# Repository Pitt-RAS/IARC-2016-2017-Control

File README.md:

IARC 2016-2017 Orbitty Shield Carrier Board

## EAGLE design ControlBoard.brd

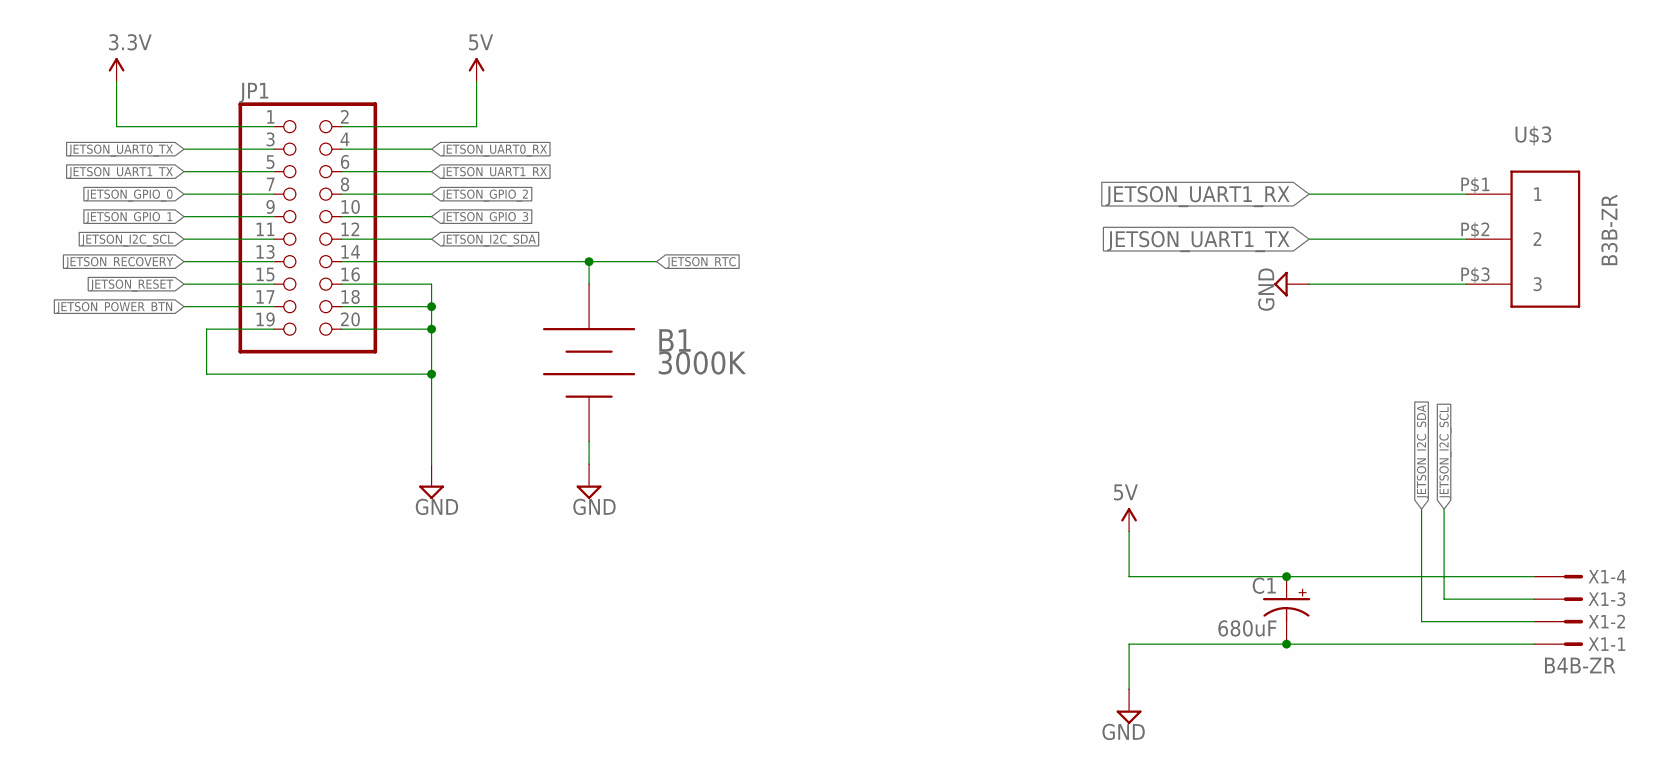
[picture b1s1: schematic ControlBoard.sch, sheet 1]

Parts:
B1: 3000K
C1: 680uF; CPOL-RADIAL-1000UF-25V
JP1: PINHD-2X10; 2X10
U$3: B3B-ZR; 3PIN-1.5MM
X1: B4B-ZR

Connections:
3.3V: JP1.1; also elsewhere on the board
5V: C1.+, JP1.2, X1.4; also elsewhere on the board
GND: B1.-, C1.-, JP1.16, JP1.18, JP1.19, JP1.20, U$3.P$3 (3), X1.1; also elsewhere on the board
JETSON_GPIO_0: JP1.7
JETSON_GPIO_1: JP1.9
JETSON_GPIO_2: JP1.8
JETSON_GPIO_3: JP1.10
JETSON_I2C_SCL: JP1.11, X1.3; also elsewhere on the board
JETSON_I2C_SDA: JP1.12, X1.2; also elsewhere on the board
JETSON_POWER_BTN: JP1.17
JETSON_RECOVERY: JP1.13
JETSON_RESET: JP1.15
JETSON_RTC: B1.+, JP1.14
JETSON_UART0_RX: JP1.4; also elsewhere on the board
JETSON_UART0_TX: JP1.3; also elsewhere on the board
JETSON_UART1_RX: JP1.6, U$3.P$1 (1)
JETSON_UART1_TX: JP1.5, U$3.P$2 (2)

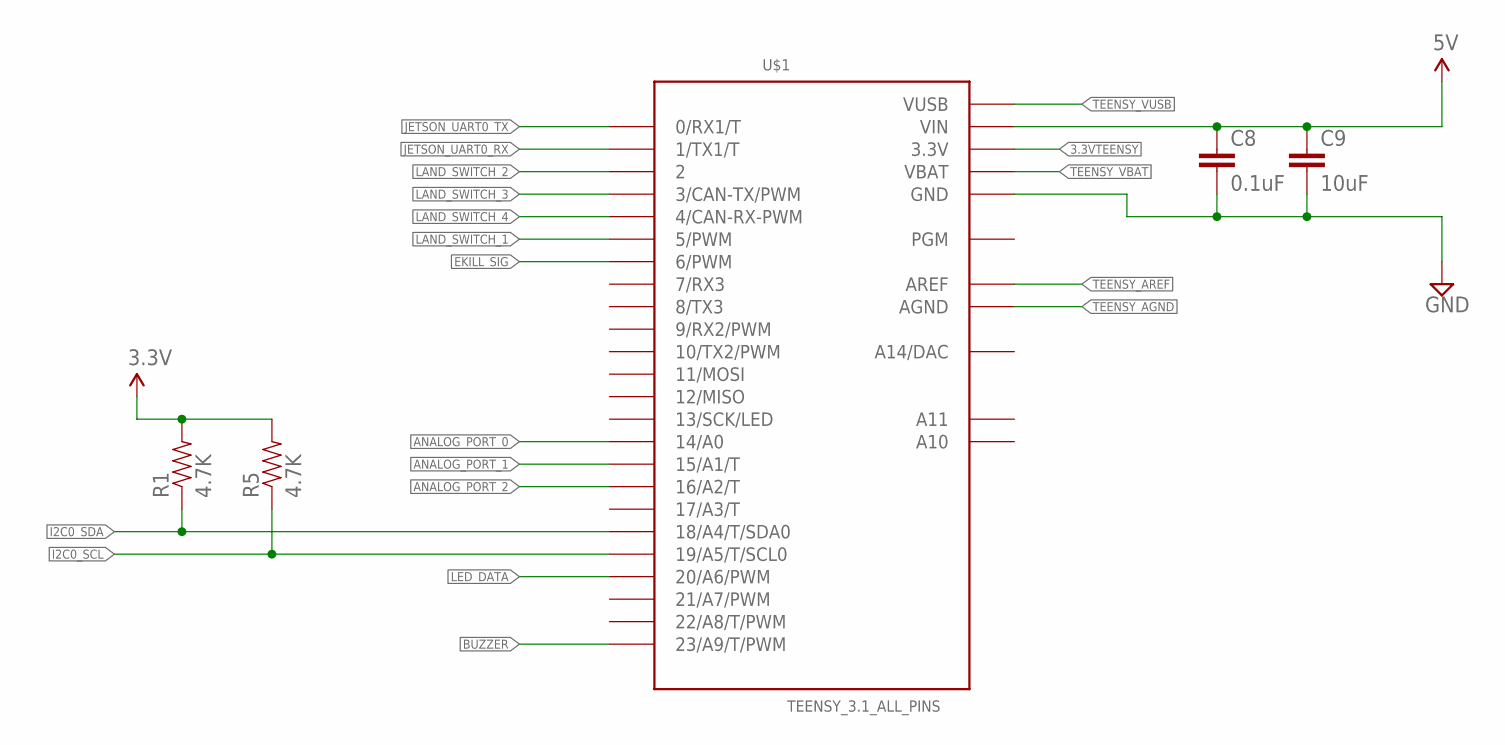
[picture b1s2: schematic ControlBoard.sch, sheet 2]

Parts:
C8: 0.1uF; 0603-CAP
C9: 10uF; 0603-CAP
R1, R5: 4.7K; 0603-RES
U$1: TEENSY_3.1_ALL_PINS; TEENSY3-ALL_PINS

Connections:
3.3V: R1.2, R5.2; also elsewhere on the board
3.3VTEENSY: U$1.3.3V, U$1.3.3V1 (3.3V)
5V: C8.1, C9.1, U$1.VIN; also elsewhere on the board
ANALOG_PORT_0: U$1.14/A0; also elsewhere on the board
ANALOG_PORT_1: U$1.15/A1 (15/A1/T); also elsewhere on the board
ANALOG_PORT_2: U$1.16/A2 (16/A2/T); also elsewhere on the board
BUZZER: U$1.23/A9 (23/A9/T/PWM); also elsewhere on the board
EKILL_SIG: U$1.6 (6/PWM); also elsewhere on the board
GND: C8.2, C9.2, U$1.GND, U$1.GND1 (GND); also elsewhere on the board
I2C0_SCL: R5.1, U$1.19/A5 (19/A5/T/SCL0); also elsewhere on the board
I2C0_SDA: R1.1, U$1.18/A4 (18/A4/T/SDA0); also elsewhere on the board
JETSON_UART0_RX: U$1.1 (1/TX1/T); also elsewhere on the board
JETSON_UART0_TX: U$1.0 (0/RX1/T); also elsewhere on the board
LAND_SWITCH_1: U$1.5 (5/PWM); also elsewhere on the board
LAND_SWITCH_2: U$1.2; also elsewhere on the board
LAND_SWITCH_3: U$1.3 (3/CAN-TX/PWM); also elsewhere on the board
LAND_SWITCH_4: U$1.4 (4/CAN-RX-PWM); also elsewhere on the board
LED_DATA: U$1.20/A6 (20/A6/PWM); also elsewhere on the board
TEENSY_AGND: U$1.AGND
TEENSY_AREF: U$1.AREF
TEENSY_VBAT: U$1.VBAT
TEENSY_VUSB: U$1.VUSB

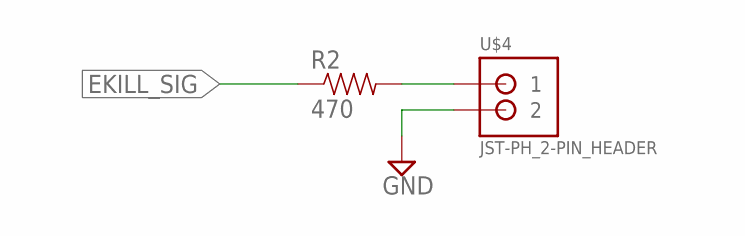
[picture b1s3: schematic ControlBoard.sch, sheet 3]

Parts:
R2: 470; 0603-RES
U$4: JST-PH_2-PIN_HEADER; JST_B2B-PH_HEADER

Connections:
EKILL_SIG: R2.1; also elsewhere on the board
GND: U$4.P2 (2); also elsewhere on the board
unnamed: R2.2, U$4.P1 (1)

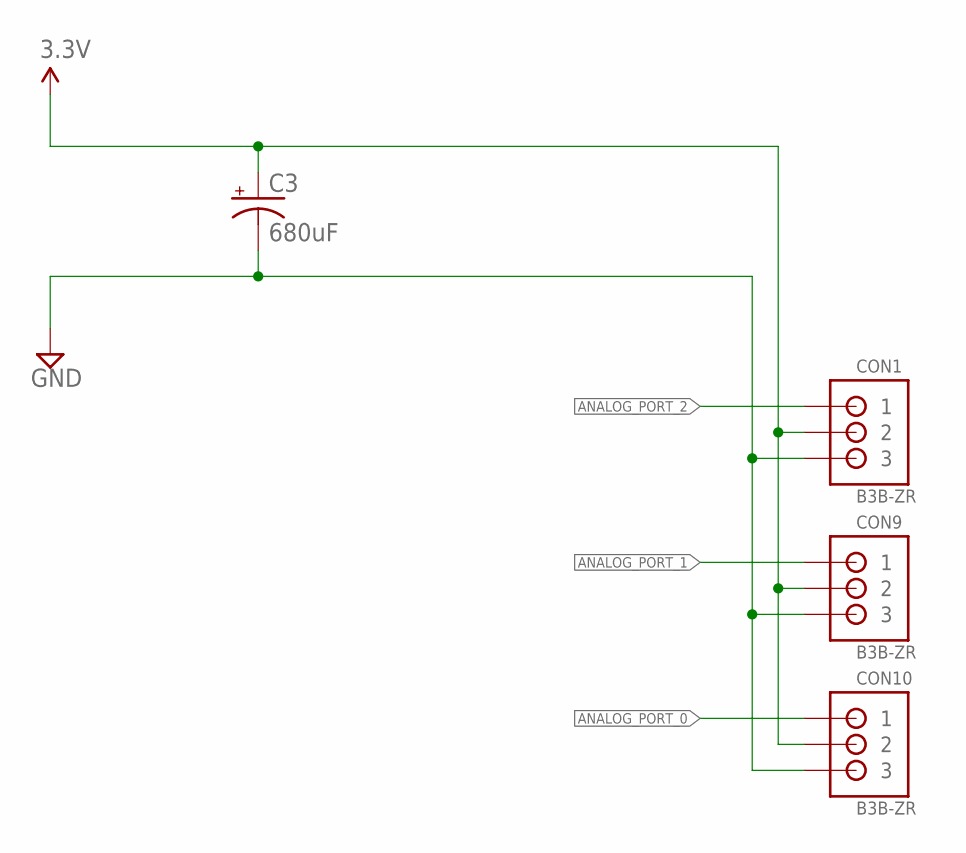
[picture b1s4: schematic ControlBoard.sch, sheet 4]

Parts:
C3: 680uF; CPOL-RADIAL-1000UF-25V
CON1, CON9, CON10: B3B-ZR

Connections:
3.3V: C3.+, CON1.2, CON9.2, CON10.2; also elsewhere on the board
ANALOG_PORT_0: CON10.1; also elsewhere on the board
ANALOG_PORT_1: CON9.1; also elsewhere on the board
ANALOG_PORT_2: CON1.1; also elsewhere on the board
GND: C3.-, CON1.3, CON9.3, CON10.3; also elsewhere on the board

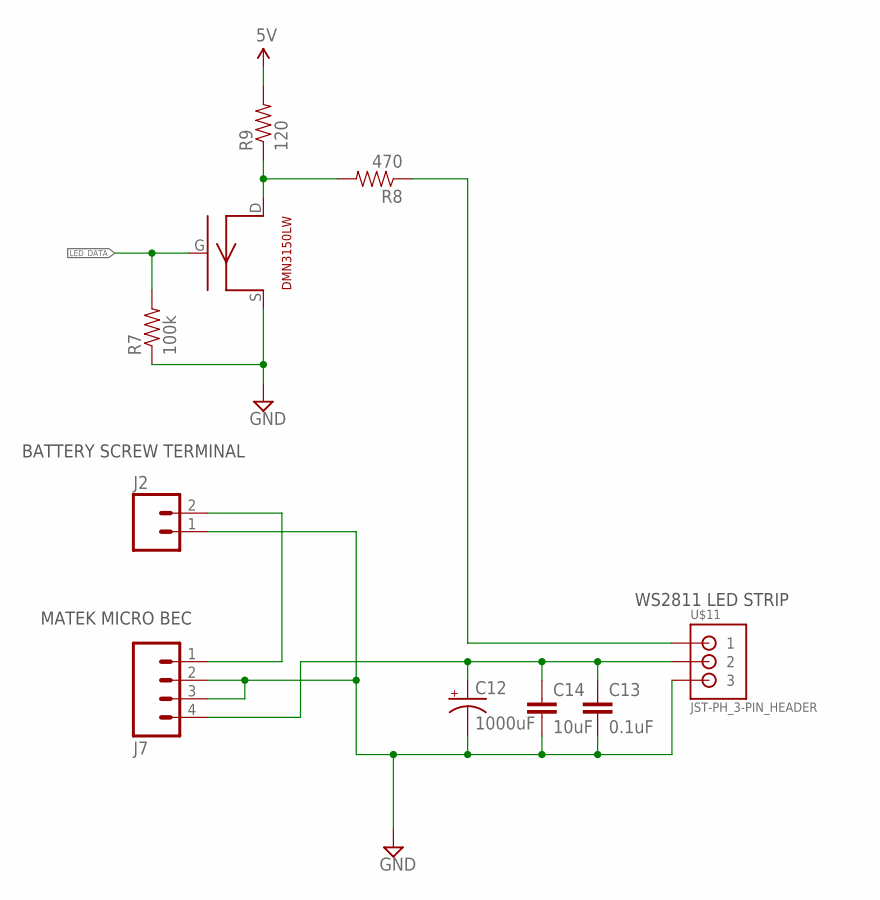
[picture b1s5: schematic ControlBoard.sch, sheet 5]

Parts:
C12: 1000uF; CPOL-RADIAL-1000UF-25V
C13: 0.1uF; 0603-CAP
C14: 10uF; 0603-CAP
J2: M025MM; SCREWTERMINAL-5MM-2
J7: M04PTH; 1X04
R7: 100k; 0603-RES
R8: 470; 0603-RES
R9: 120; 0603-RES
U$2: DMN3150LW
U$11: JST-PH_3-PIN_HEADER; JST_B3B-PH_HEADER

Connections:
5V: R9.2; also elsewhere on the board
GND: C12.2 (-), C13.2, C14.2, J2.1, J7.2, J7.3, R7.1, U$2.S, U$11.P3 (3); also elsewhere on the board
LED_DATA: R7.2, U$2.G; also elsewhere on the board
unnamed: J2.2, J7.1
unnamed: C12.1 (+), C13.1, C14.1, J7.4, U$11.P2 (2)
unnamed: R8.1, U$11.P1 (1)
unnamed: R8.2, R9.1, U$2.D

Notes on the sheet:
BATTERY SCREW TERMINAL
MATEK MICRO BEC
WS2811 LED STRIP

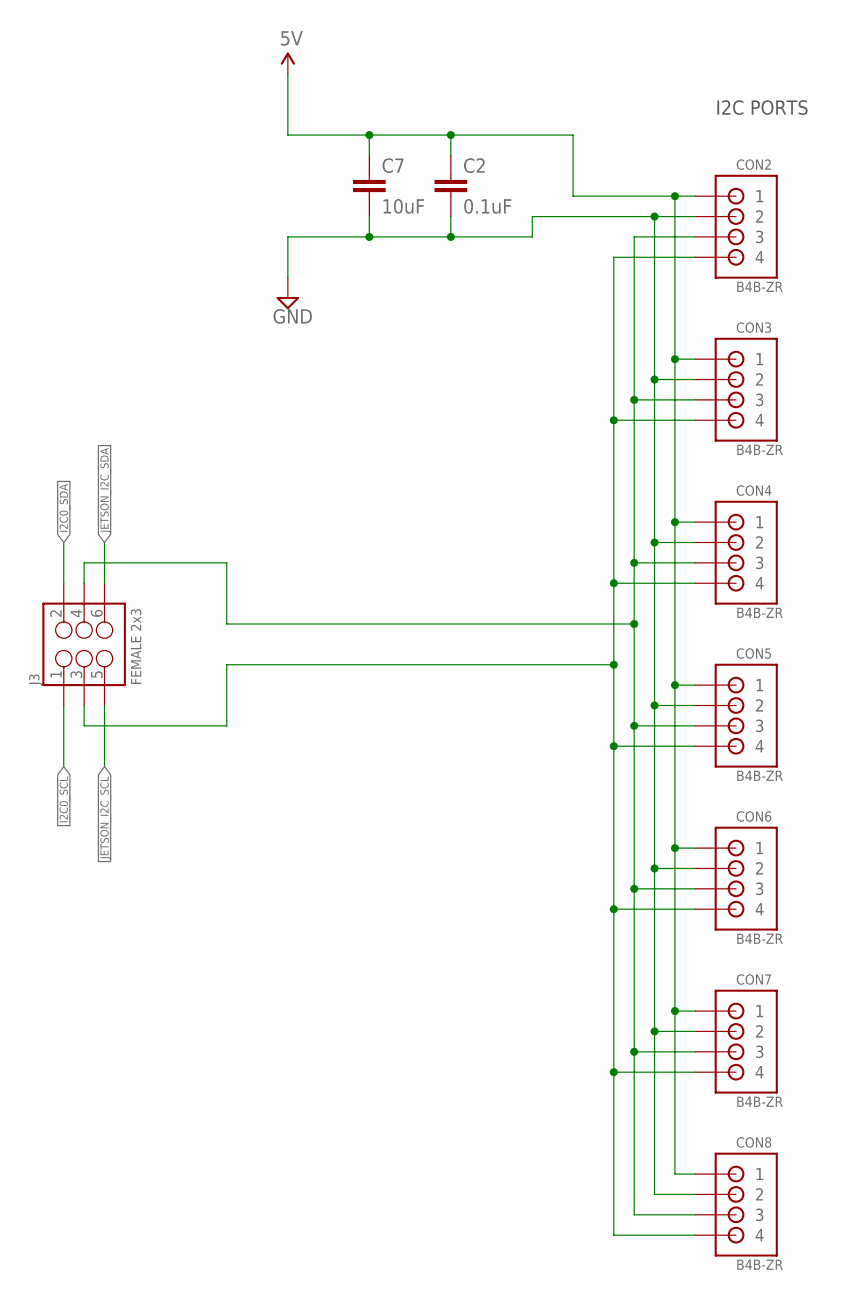
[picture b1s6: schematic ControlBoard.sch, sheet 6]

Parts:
C2: 0.1uF; 0603-CAP
C7: 10uF; 0603-CAP
CON2, CON3, CON4, CON5, CON6, CON7, CON8: B4B-ZR
J3: FEMALE 2x3; 2X3

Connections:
5V: C2.1, C7.1, CON2.1, CON3.1, CON4.1, CON5.1, CON6.1, CON7.1, CON8.1; also elsewhere on the board
GND: C2.2, C7.2, CON2.2, CON3.2, CON4.2, CON5.2, CON6.2, CON7.2, CON8.2; also elsewhere on the board
I2C0_SCL: J3.1; also elsewhere on the board
I2C0_SDA: J3.2; also elsewhere on the board
JETSON_I2C_SCL: J3.5; also elsewhere on the board
JETSON_I2C_SDA: J3.6; also elsewhere on the board
N8: CON2.4, CON3.4, CON4.4, CON5.4, CON6.4, CON7.4, CON8.4, J3.3
N9: CON2.3, CON3.3, CON4.3, CON5.3, CON6.3, CON7.3, CON8.3, J3.4

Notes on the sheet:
I2C PORTS

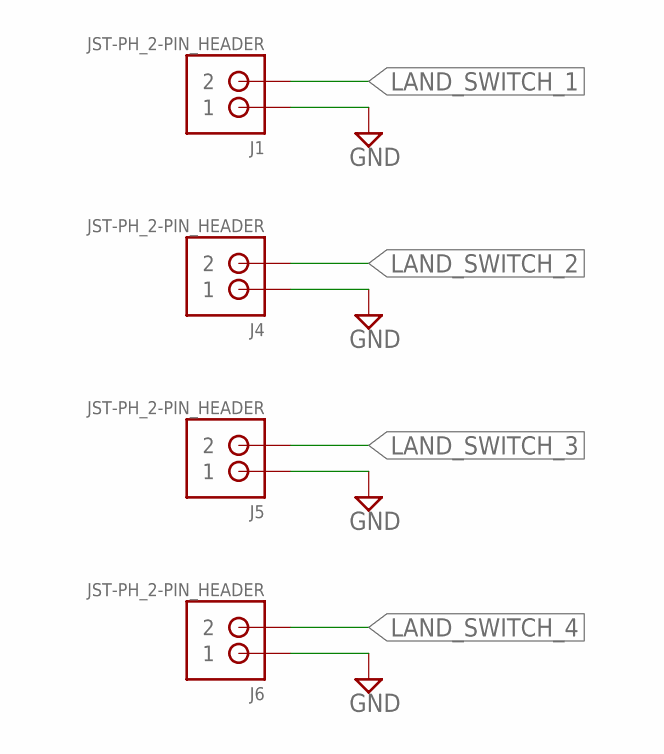
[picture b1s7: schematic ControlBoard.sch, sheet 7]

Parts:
J1, J4, J5, J6: JST-PH_2-PIN_HEADER; JST_B2B-PH_HEADER

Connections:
GND: J1.P1 (1), J4.P1 (1), J5.P1 (1), J6.P1 (1); also elsewhere on the board
LAND_SWITCH_1: J1.P2 (2); also elsewhere on the board
LAND_SWITCH_2: J4.P2 (2); also elsewhere on the board
LAND_SWITCH_3: J5.P2 (2); also elsewhere on the board
LAND_SWITCH_4: J6.P2 (2); also elsewhere on the board

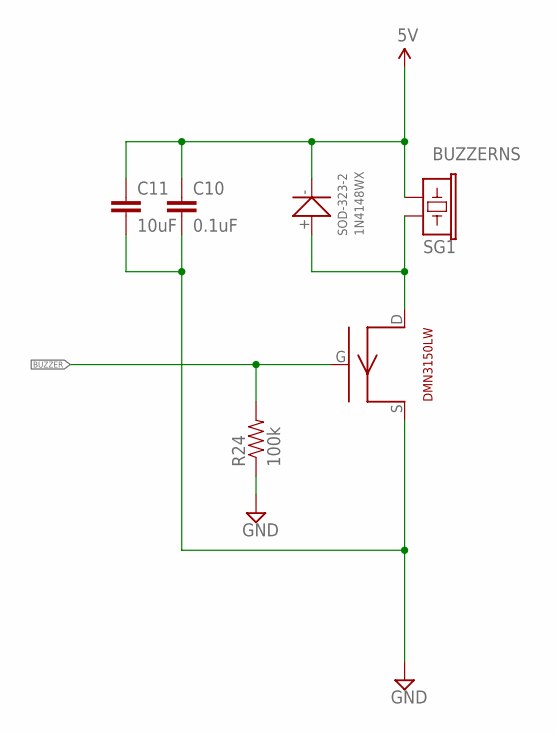
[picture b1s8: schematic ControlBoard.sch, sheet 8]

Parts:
C10: 0.1uF; 0603-CAP
C11: 10uF; 0603-CAP
R24: 100k; 0603-RES
SG1: BUZZERNS; BUZZER-12MM-NS
U$8: 1N4148WX_SOD-323-2
U$9: DMN3150LW

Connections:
5V: C10.1, C11.1, SG1.+ (1), U$8.-; also elsewhere on the board
BUZZER: R24.2, U$9.G; also elsewhere on the board
GND: C10.2, C11.2, R24.1, U$9.S; also elsewhere on the board
unnamed: SG1.- (2), U$8.+, U$9.D

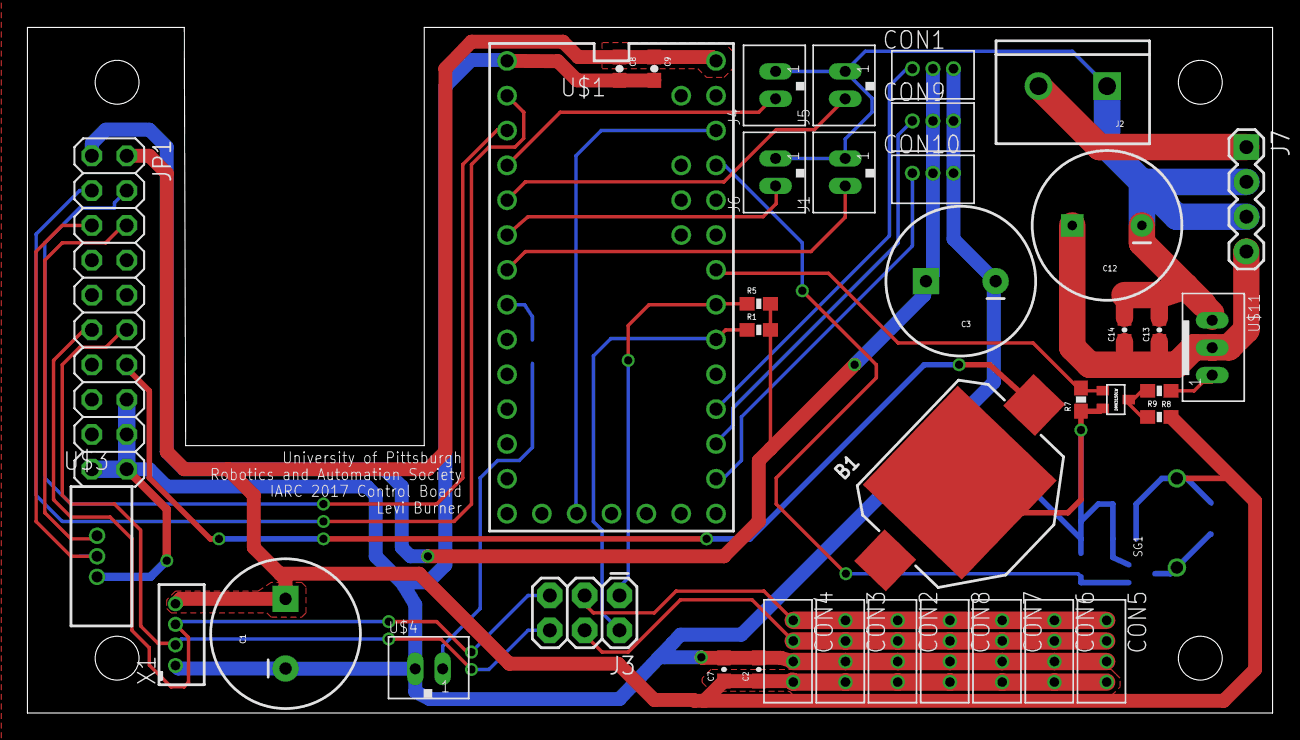
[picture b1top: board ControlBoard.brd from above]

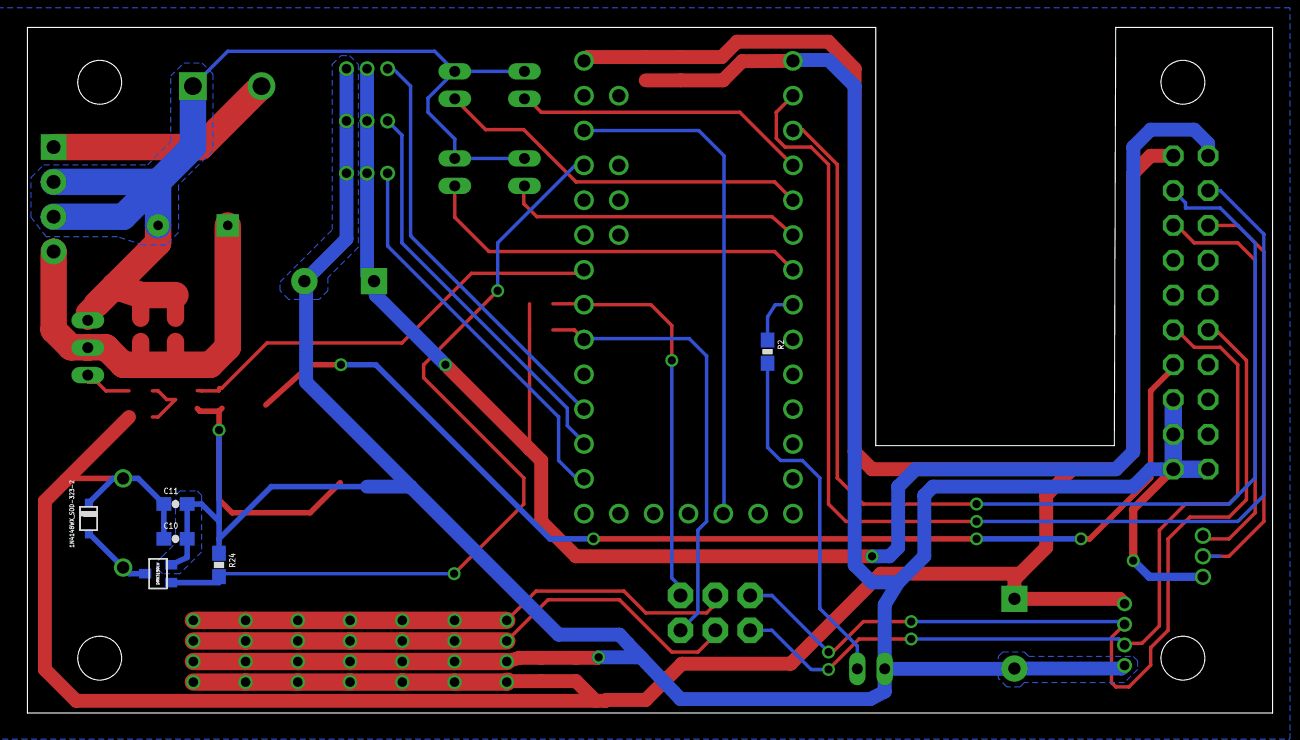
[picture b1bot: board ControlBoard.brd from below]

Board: 2 copper layers, 90.8 x 50.0 mm, 46 parts (6 on the bottom side), 31 nets.

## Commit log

2017-04-11 V1 Orbitty Shield
2017-04-11 Add license and readme
2017-04-11 Fix board outline and add name

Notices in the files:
parts and their libraries:
SparkFun-Capacitors: Licensing: Creative Commons ShareAlike 4.0 International - https://creativecommons.org/licenses/by-sa/4.0
